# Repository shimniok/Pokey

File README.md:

# Pokey

Pokey is the firefighting robot I entered into the 2007 Front Range Robotics Firefighting Challenge. It lost. But I've been
revising and improving it over the years.

I've also been using it to demonstrate robotics to lots and lots of children and quite a few adults at various robotics
expos like Robots At The Hangar, Denver Mini Maker Faire, and so on.  The kids love it. :)

# Directories

 * ff - is the main code base that I'm writing from scratch
 * encoders - scratch area for me playing with encoders
 * simple-test - is a simple led blinky, mostly for me playing
 * demo - some basic demonstration functionality, mostly for me playing

# Details

The basic Pokey Design uses a Pololu Orangutan LV168 with ATmega168 onboard. I'm using the old libpololu-avr library.

## Pinout

See LV168_Pinout.png

 * PC0 (PCINT8) - Right Encoder
 * PC1 (PCINT9) - Left Encoder

## Drivetrain

The robot has differential drive, using Tamiya 70168 Double Gearbox with low voltage Mabuchi motors.

## Chassis

The chassis is made of 1/4" funiture-grade plywood (or if I update it, hobby-grade plywood)

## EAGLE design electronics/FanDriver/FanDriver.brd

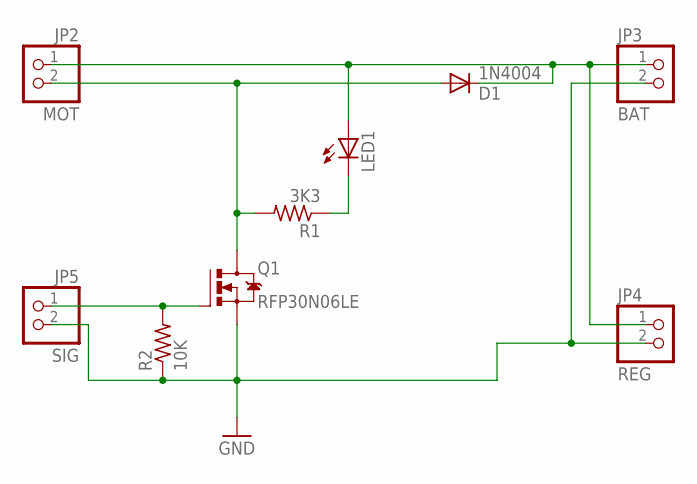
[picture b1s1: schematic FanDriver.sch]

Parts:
D1: 1N4004; DO41-10
JP2: MOT; 1X02-S
JP3: BAT; 1X02-S
JP4: REG; 1X02-S
JP5: SIG; 1X02-S
LED1: LEDCHIPLED_1206; CHIPLED_1206
Q1: RFP30N06LE; TO220BV
R1: 3K3; R0603
R2: 10K; R0603

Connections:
GND: JP3.2, JP4.2, JP5.2, Q1.S, R2.1
M2: D1.A, JP2.2, Q1.D, R1.2
unnamed: LED1.C, R1.1
SIG: JP5.1, Q1.G, R2.2
VBAT: D1.C, JP2.1, JP3.1, JP4.1, LED1.A

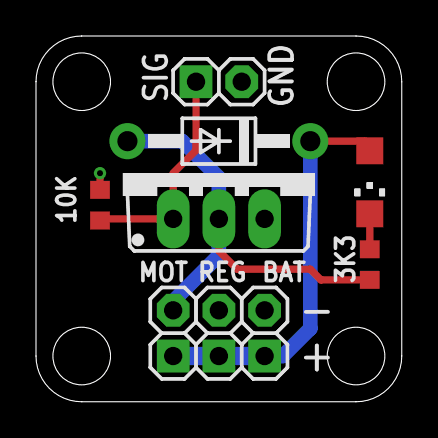
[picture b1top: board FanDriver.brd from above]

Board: 2 copper layers, 20.3 x 20.3 mm, 9 parts (0 on the bottom side), 5 nets.

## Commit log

2015-03-05 Initial version
2015-03-27 Implemented ack parameter for write (master); implemented I2C automatic write/read bit addressing; converted args to const
2015-03-27 added gitignore file
2015-03-27 Added makefile
2015-03-27 restored camcom.h to gbcam subdir
2015-03-27 Add license
2015-03-27 Merged in old ff subdir into master project
2015-03-27 Initial commit for demo, encoders (testing), simple-test
2015-03-27 Added pinout diagrams
2015-03-27 added detail to readme
2015-03-27 updated gitignore
2015-03-27 updated readme for readability
2015-03-27 updated pinout drawings with background color
2015-03-27 added encoder handler, variables, init
2015-03-27 moved servo/esc controller to C2, restored initialization
2015-03-28 initial version of fan driver board
2015-03-28 updated gitignore with eagle files
2015-03-30 converted code to use plain mosfet vs. esc for fan control
